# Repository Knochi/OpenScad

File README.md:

# OpenScad

A loose collection of Modules for OpenScad

## Resources

<https://openhome.cc/eGossip/OpenSCAD/>

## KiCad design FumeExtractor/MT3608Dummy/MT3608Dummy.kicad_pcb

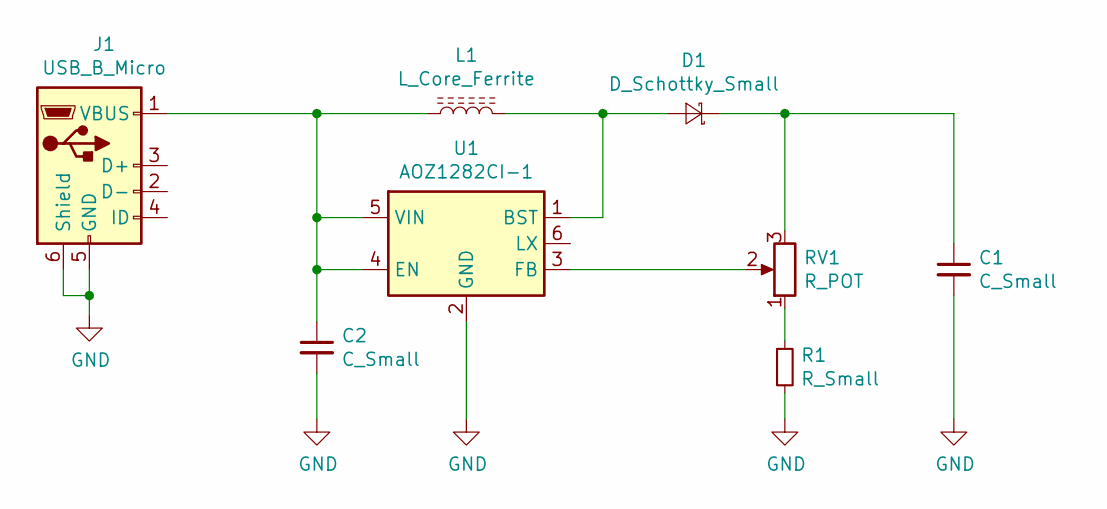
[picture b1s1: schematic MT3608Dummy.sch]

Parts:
C1, C2: C_Small; C_1206_3216Metric
D1: D_Schottky_Small; D_SOD-123
J1: USB_B_Micro; USB_Micro-B_Molex_47346-0001
L1: L_Core_Ferrite; L_Bourns-SRN8040_8x8.15mm
R1: R_Small; R_0805_2012Metric
RV1: R_POT; Potentiometer_Bourns_3299P_Horizontal
U1: AOZ1282CI-1; SOT-23-6

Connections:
GND: C1.2, C2.2, J1.5 (GND), J1.6 (Shield), R1.2, U1.2 (GND)
unnamed: C1.1, D1.1 (K), RV1.3
unnamed: C2.1, J1.1 (VBUS), L1.1, U1.4 (EN), U1.5 (VIN)
unnamed: D1.2 (A), L1.2, U1.1 (BST)
unnamed: R1.1, RV1.1
unnamed: RV1.2, U1.3 (FB)

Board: 2 copper layers, 8 parts (0 on the bottom side), 6 nets, no tracks yet.

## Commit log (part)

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2023-03-08 updated tile dimensions
2023-03-09 just commented
2023-03-10 fine tuned kerf
2023-03-10 added Wago_2601 terminal
2023-03-15 JST Pliers to remix
2023-03-15 added source comment
2023-03-16 handle created
2023-03-16 started desing of the jaws
2023-03-23 initial commit for BambuLab P1P Design Contest. A customizable Modplate!
2023-03-23 fixed placement
2023-03-24 added lego and hex patterns
2023-03-24 first render
2023-03-24 created new reduced scad and few render for upload
2023-04-05 added THT capacitor
2023-04-26 change to deckmate adapter
2023-04-26 some modifikations repaired the original stl
2023-04-26 pi Pico changed zOffset
2023-04-26 start gridfinity design
2023-05-02 AlienRPG box organizer
2023-05-02 Gridfinity stuff
2023-05-02 splitted card tray for sleeved cards
2023-05-04 fixed doveTail
2023-05-04 fixed the width
2023-05-08 added dicetray and dualTray
2023-05-08 added the dovetailtest to export
2023-05-08 printed first dicetray
2023-05-09 added option for general tray
2023-05-09 added dualcardtray to export
2023-05-10 various changes
2023-05-10 introduced floorthck
2023-05-15 housekeeping
2023-05-15 added protection nozzle for USB scope prototype.
2023-05-15 create STL
2023-06-20 LawnMoverbolt added
2023-06-20 added usbscopeprotector
2023-06-20 added option for embedded nut
2023-06-29 added common OLED module moduile
2023-06-29 finished 1.3inch OLED module fixed MPE_087 pin height
2023-06-29 oled finetuning
2023-06-30 added first freecad modification
2023-09-05 added stuff
2023-09-05 started WM686 relay
2023-09-05 some parts for fiverr projects
2023-09-17 added wuerth redcubes
2023-11-14 this and that
2023-11-20 added 7segment display model
2023-11-20 added pads
2023-11-20 Flange for the Wiper
2023-11-20 some eCad stuff
2023-11-20 tuning
2023-11-29 added 7segment display
2023-11-29 added model for candle holder with nail
2023-12-06 created a replacment clamp part for eQ3Thermostat
2023-12-06 adapter to apply naiös to candles
2023-12-19 added SNR coil
2023-12-20 more tries on thermostat clamp
2024-01-31 Some stuff added
2024-01-31 fiverr stuff and others
2024-02-01 added n-gon module
2024-02-02 added Housing for two G5sockets
2024-02-02 nGon is displayed as sample
2024-02-05 finished
2024-02-05 start project
2024-02-05 new paramaeter
2024-02-21 part to prevent toilet paper from running out
2024-02-21 magnet plate for Omnifixo
2024-02-21 an adapter to use the modCase with the SteamDeck Dock from JSAUX
2024-02-21 some updates
2024-02-28 split version of radius measure tool thing 4709316
2024-02-28 Stuff
2024-02-29 added magnets and mini version
2024-02-29 added 1206 reverse package
2024-03-06 started flanged box
2024-03-07 chamfered box done
2024-03-07 TFT35 case
2024-03-08 renamed
2024-03-08 rena,ed
2024-03-08 started USB-C upright
2024-03-08 test for screen offset issue
2024-03-08 split RMT done
2024-04-26 libraries.. cleanup
2024-04-26 Start C3_BB droid
2024-04-26 Overhead Closet planning
2024-04-26 MarbleClock remix
2024-04-26 chamfered box
2024-05-02 continued work on C3_bb
2024-05-02 more work on BB8
2024-05-08 added foundry robot remix
2024-05-08 convertet icons to 64px
2024-05-08 added 64px sprite sheet
2024-05-08 add discordicon
2024-06-10 first prototype
2024-06-10 renamed the icons
2024-06-16 updated for sturdy mount
2024-06-19 made some new stuff
2024-06-21 modified OLED example
2024-06-21 new project - joes paper forming tool
2024-06-21 first delivery
2024-06-21 added module to bend the flex
2024-06-21 delivery
2024-07-01 added fisher AKG stls
2024-07-01 forming tool and other changes
2024-07-10 added a knob
2024-07-10 made it more printable
2024-07-19 gsdfhtfghtr
2024-07-23 started the HexpropelloDodecahedron work
2024-07-24 added height calculation
2024-07-24 changed some values
2024-07-24 started ferrite
2024-07-24 finished the pentaTile
2024-07-25 added pointonline function
2024-07-26 added fuse
2024-07-26 finished TDK boppin
2024-08-01 changes changes...
2024-08-09 SCHTUFF
2024-08-09 some changes
2024-10-16 moep
2024-10-16 added holder
2024-10-16 new project - kitchen drawer
2024-10-25 first proto of punchjg added kerf correction for topFrame
2024-10-25 added kerf to all rack and pinions
2024-11-11 new stuff
2024-11-11 added top
2024-11-11 couchhooks
2024-11-21 updated lifeCounter
2024-11-21 some new exports
2024-11-21 Fanadapter for 9733 with snaps
2024-11-21 start of LED version
2024-11-21 ready to print
2024-11-22 9733 Fan to 20x20 profile
2024-11-22 Remix of RadiusGauge Box for A1Mini
2024-12-04 added some Multiboard stuff
2024-12-04 2WayFanshrout for Fiverr customer
2024-12-04 Fan adapter for VWIF Demo
2024-12-04 close the holes in my outdoor lanterns
2024-12-04 Magnetic Gunstock initial import
2024-12-04 start remixing Multiboard stuff
2024-12-04 merged objects
2024-12-04 started Multiboard scad designs
2024-12-04 started MB drawer development
2024-12-05 start MultiBoard Light
2024-12-05 added snaps
2024-12-06 improvemts
2024-12-06 added labels
2024-12-06 added embedded magnet option
2024-12-06 split in two halves for coloring or embedding
2024-12-06 tuned facets to match roundings
2024-12-06 spacing
2024-12-10 added support for different bottom sized fans
2024-12-10 magnet holder
2024-12-13 something
2024-12-13 added some parameters
2024-12-13 embedded magnet
2024-12-20 new project
2024-12-20 little progress
2024-12-20 Phillip Poisel Hueforge
2024-12-20 lots of hcanges
2024-12-20 added base and single layer rendering
2024-12-20 new render with correct Layer hights and shifts
2025-01-07 modifier to fix mini bambuspool
2025-01-07 moved modifier to the correct position
2025-01-08 new adapter
2025-01-08 added upright slot for label
2025-01-09 added new vertical label slot
2025-01-09 shelf mount for A1 Mini
2025-01-10 start multipoint slot for customizable brickholder
2025-01-10 Magnetic Gunstock CleanUp
2025-01-10 new Accessories
2025-01-10 KLIPPT
2025-01-10 new order
2025-01-10 chchchaaaaanges
2025-01-10 Multiboard and powerbrick
2025-01-14 okok
2025-01-16 new customizables
2025-01-16 changees
2025-01-16 fixed ri2ro
2025-01-16 TS80PHolder finish
2025-01-28 UnderDogs Coin
2025-02-05 custoizer for SpoolStand labels
2025-02-05 added narrow spool stand remix
2025-02-05 mew projects
2025-02-06 More modifications
2025-02-07 new projects
2025-02-07 some more changes
2025-02-07 Delivered Tap Handle
2025-02-24 Coreclain Challenge
2025-02-24 New Keyring
2025-02-24 So adapter
2025-02-24 another keyring
2025-02-26 start
2025-02-27 added dents for descinacent use
2025-02-27 Corcelainchallenge
2025-02-27 another nameplate
2025-02-28 ready for first publish
2025-03-11 new fiverr order
2025-03-14 new name pendant
2025-03-18 stuff added
2025-03-18 delivered
2025-03-19 finish enclosure
2025-03-20 fixed seal
2025-04-01 own name pendenat for reddit
2025-04-01 downloaded cyberbrick models
2025-04-07 optimzed front and added lcd
2025-04-15 added DIP switch
2025-04-15 Fiverr order
2025-04-16 added
2025-04-16 fiverr delivery
2025-04-16 new component for fiverr customer
2025-04-17 added wirevcomb from thingiverse
2025-04-29 moved
2025-05-05 modified for A1Mini
2025-05-05 just a test
2025-05-07 did something
2025-05-07 don't know what this is for
2025-05-07 new take on the piggybang
2025-05-08 changed the attachment angle
2025-05-08 cleanup
2025-05-19 backup
2025-05-20 mass import
2025-05-23 after the mess
2025-06-08 cable label new
2025-06-08 added a few more features
2025-06-13 added option for non-round cables
2025-06-17 MacroLens Adapter for MultiBoom
2025-06-17 arms and grommets
2025-06-17 rework cold shoe
2025-06-18 added springs
2025-06-24 new user, new version
2025-06-25 thisnadnthe
2025-06-25 dumbbellmold
2025-06-26 New design
2025-07-01 finished solarDrain
2025-07-01 presented result do buyer (not delivered)
2025-07-01 send this to buyer
2025-07-02 adapter
2025-07-02 finsihed
2025-07-03 printed and works
2025-07-18 made first proto
2025-07-18 gbr to measure things
2025-07-18 duuuh
2025-07-19 wuutwuut
2025-07-28 burp
2025-08-01 update bosl
2025-08-03 added extra clearance
2025-08-03 merge
2025-08-08 new name tag
2025-08-13 tackling char by char
2025-08-13 finished hanger, started waterfall
2025-08-13 yeah waterfall
2025-09-08 add SMC capacitor for MichaelH
2025-09-08 files for EcoFlow Contest
2025-09-08 updated BOSL
2025-09-08 updateupdate
2025-09-12 added option to split plates
2025-09-12 added hanger for pump
2025-09-12 added a pcb in the back
2025-09-12 small adaptions
2025-09-20 New Picture Frame model
2025-09-20 small change
2025-10-15 some more test exports
2025-10-15 started with antenna
2025-10-15 updated BOSL2
2025-10-21 spool saver
2025-11-10 whoooop
2025-11-10 cleanup of submodules
2025-11-18 kazong
2025-11-24 added new connectors
2025-11-24 start jig
2025-11-24 freeCAD
2025-11-24 Fiverr customer
2025-11-24 connectors
2025-11-24 for electgroplating
2025-11-28 new Fiverr project
2025-11-28 china housing
2025-12-01 finished jig
2025-12-02 spinnereien
2025-12-02 new coil
2025-12-02 exported
2025-12-02 another one
2025-12-03 jig improvments
2025-12-03 added spacings and minimal wall thickness
2025-12-11 added display bumper
2025-12-11 finished bumper
2025-12-11 usb-c cutaway
2026-01-05 added pusher
2026-01-13 delivery2
2026-01-13 added a connection box
2026-01-13 custom arm
2026-01-13 new creation
2026-01-13 modified
2026-01-13 ignore BOSL2
2026-01-13 printed and works!
2026-01-13 updated documentation
2026-01-13 new fiver job
2026-01-29 latest iteration
2026-01-29 send to manufacturing
2026-01-29 embedded logo
2026-02-04 example
2026-02-05 made it work with trailing
2026-04-21 Girls Day PCB Housing and Parts Tray
2026-04-21 Drilljig final version
2026-04-21 fixed
2026-04-21 some more gigs completet
2026-04-21 found some issues, again
2026-04-22 added a pin to remove PCB
2026-04-22 some improvments
2026-04-22 merged
2026-04-22 merged again
2026-04-29 A1Mini Version of Biermoerser
2026-04-29 added a coincellholder
2026-04-29 tunings
2026-04-30 split lever
2026-04-30 add stl
2026-06-17 update all
2026-06-24 new candle
2026-06-24 woosh
